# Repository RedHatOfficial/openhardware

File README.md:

# openhardware

This repository contains the sources for Red Hat's "blinky" hardware giveaway for the Open Hardware Summit 2018.

Board files (.brd/.sch) are under the CERN Open Hardware License v1.2, except for some libraries embedded from SparkFun, which are under the 
CC-BY-SA license.

Source code (.ino) is GPLv2 or later.

All documentation is under the CC-BY-SA license.

Red Hat, and the Shadowman logo are registered trademarks of Red Hat, Inc, and no special permission is granted to use these marks as part of 
this licensing.

Thanks to Alicia Gibb and Nathan Seidle for creating this awesome kit!

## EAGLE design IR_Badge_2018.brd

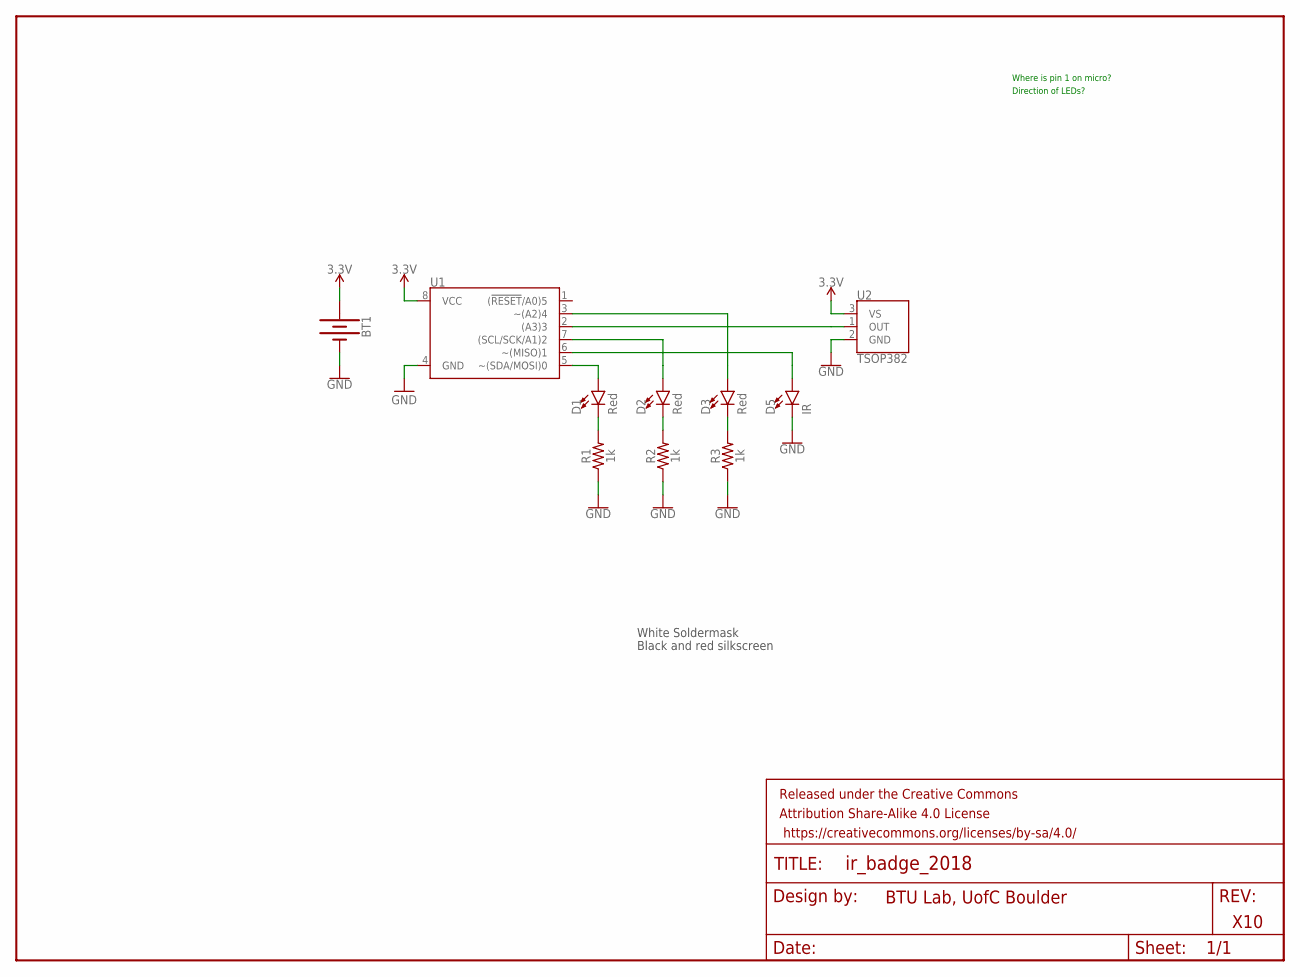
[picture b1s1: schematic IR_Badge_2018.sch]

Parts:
BT1: BATTERY-20MM_PTH; BATTCOM_20MM_PTH
D1, D2, D3: Red; LED_5MM_EXTRASILK
D5: IR; LED_5MM_NOSILK
FRAME1: FRAME-LETTER; CREATIVE_COMMONS
R1, R2, R3: 1k; RESISTOR
U1: ATTINY85-ARDUINODIP; DIP-8
U2: TSOP382; TSOP382-HORIZONTAL

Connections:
3.3V: BT1.1 (+), U1.8 (VCC), U2.3 (VS)
GND: BT1.2 (-), D5.K (C), R1.P$1 (1), R2.P$1 (1), R3.P$1 (1), U1.4 (GND), U2.2 (GND)
unnamed: D1.A, U1.5 (~(SDA/MOSI)0)
unnamed: D2.A, U1.7 ((SCL/SCK/A1)2)
unnamed: D1.K (C), R1.P$2 (2)
unnamed: D3.A, U1.3 (~(A2)4)
unnamed: D2.K (C), R2.P$2 (2)
unnamed: D3.K (C), R3.P$2 (2)
unnamed: D5.A, U1.6 (~(MISO)1)
unnamed: U1.2 ((A3)3), U2.1 (OUT)

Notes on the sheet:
X10
BTU Lab, UofC Boulder
White Soldermask
Black and red silkscreen
Where is pin 1 on micro?
Direction of LEDs?

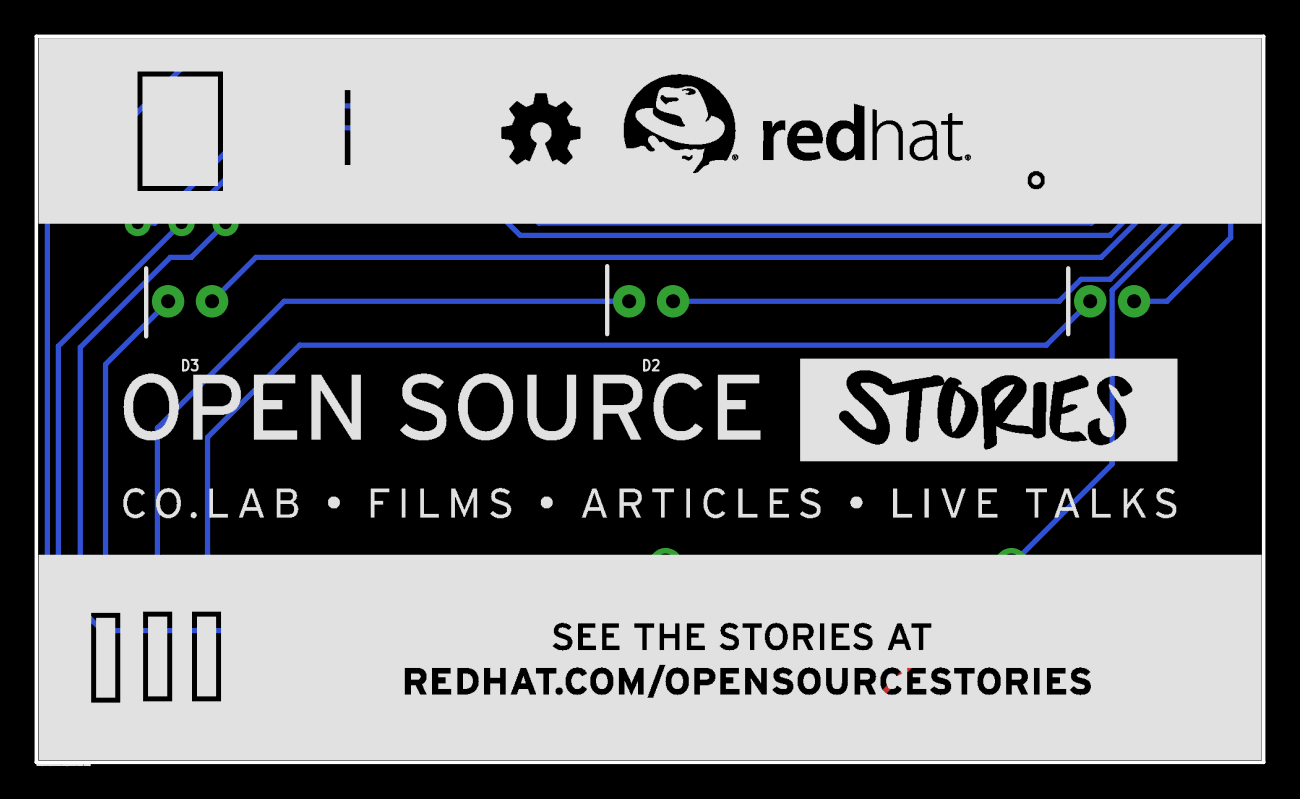
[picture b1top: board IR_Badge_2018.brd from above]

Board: 2 copper layers, 71.0 x 42.0 mm, 11 parts (1 on the bottom side), 10 nets.

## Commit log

2018-09-18 correct licensing
2018-09-18 add build instructions pdf

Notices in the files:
parts and their libraries:
SparkFun-Aesthetics: Licensing: Creative Commons ShareAlike 4.0 International - https://creativecommons.org/licenses/by-sa/4.0
SparkFun-Aesthetics: Released under the Creative Commons Attribution Share-Alike 4.0 License
SparkFun-Aesthetics: https://creativecommons.org/licenses/by-sa/4.0
